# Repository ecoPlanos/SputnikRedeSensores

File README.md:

# SputnikRedeSensores

Open source project of a sensors test suit.

The goal is to develop a system to compare several sensors of each type out of several types.
The sensors will be assembled on a PCB for each type, that will connect to an Arduino Due compatible shield.
A program running on the Arduino, will log sensors data to a SD card and make it accessible through a FTP server.

types of sensors:
Temperature and relative humidity;
Superficial temperature;
Motion detection;
Air quality;
Electrical current;
Water flow;
Proximity;
Distance;
Microwave;
Lumen;
UV.

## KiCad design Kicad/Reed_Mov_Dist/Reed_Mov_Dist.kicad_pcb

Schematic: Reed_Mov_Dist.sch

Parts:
C1: 10uF; CP_Radial_D4.0mm_P2.00mm
C2: 220uF; CP_Radial_D7.5mm_P2.50mm
D1: D; D_T-1_P5.08mm_Horizontal
J1: Barrel_Jack; BARREL_JACK
J2, J3, J4, J13: Conn_01x02; Socket_Strip_Straight_1x02_Pitch2.54mm
J5: LIS3DH_1; Socket_Strip_Straight_1x06_Pitch2.54mm
J6: ITG3200; Socket_Strip_Straight_1x06_Pitch2.54mm
J7: LIS3DH_2; Socket_Strip_Straight_1x06_Pitch2.54mm
J8: TTL_Level_Shifter_1; Socket_Strip_Straight_1x06_Pitch2.54mm
J9: TTL_Level_Shifter_2; Socket_Strip_Straight_1x06_Pitch2.54mm
J10: HC-SRO4; Socket_Strip_Straight_1x04_Pitch2.54mm
J11: URM37; Socket_Strip_Straight_1x09_Pitch2.54mm
J12: LV-MaxSonar-EZ1; Socket_Strip_Straight_1x07_Pitch2.54mm
R1, R2, R3: 1K; R_Axial_DIN0207_L6.3mm_D2.5mm_P7.62mm_Horizontal
U1: LM7805_TO220; TO-220-3_Vertical
U2: XBEE
uP1: ARDUPROMINI-6; ArduProMini-6

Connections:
3V3: J6.1, J7.5, J8.1, J12.6, J13.2, R1.1, R2.1, R3.1, uP1.22
3V3_Xbee: J13.1, U2.1 (VCC)
5V: C1.1, J9.1, J10.1, J11.9, U1.3 (VO), uP1.19
ADC_EZ1: J12.3, uP1.26
ECHO_EZ1: J12.2, uP1.25
ECHO_HC: J8.3, uP1.16
ECHO_HC_HV: J9.3, J10.3
ECHO_URM: J8.5, uP1.18
ECHO_URM_HV: J9.5, J11.6
GND: C1.2, C2.2, J1.2, J1.3, J2.1, J3.1, J4.1, J5.6, J6.2, J7.6, J8.6, J9.6, J10.4, J11.8, J12.7, U1.2 (GND), U2.10 (GND), uP1.10, uP1.20
unnamed: C2.1, D1.1 (K), U1.1 (VI)
unnamed: D1.2 (A), J1.1
Reed_Big_White: J3.2, R2.2, uP1.12
Reed_Red: J2.2, R1.2, uP1.11
Reed_Small_White: J4.2, R3.2, uP1.13
Rx: U2.2 (DOUT), uP1.8
SCL: J6.4, J7.3, uP1.31
SDA: J6.3, J7.4, uP1.32
TRIG_EZ1: J12.4, uP1.29
TRIG_HC: J8.2, uP1.15
TRIG_HC_HV: J9.2, J10.2
TRIG_URM: J8.4, uP1.17
TRIG_URM_HV: J9.4, J11.4
Tx: U2.3 (DIN), uP1.7

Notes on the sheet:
Reed Sensors
Arduino Pro Mini
Distance Sensors
Accelerometers
Power Supply

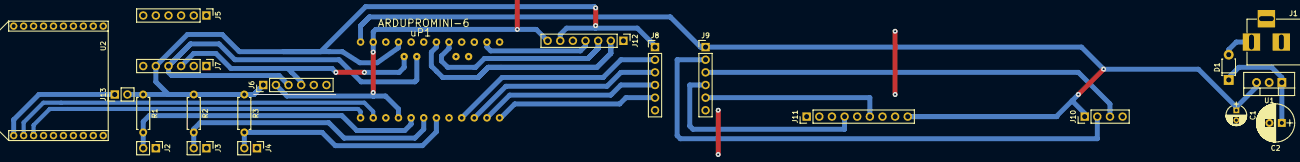
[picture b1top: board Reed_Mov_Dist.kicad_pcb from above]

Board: 2 copper layers, 22 parts (0 on the bottom side), 24 nets.

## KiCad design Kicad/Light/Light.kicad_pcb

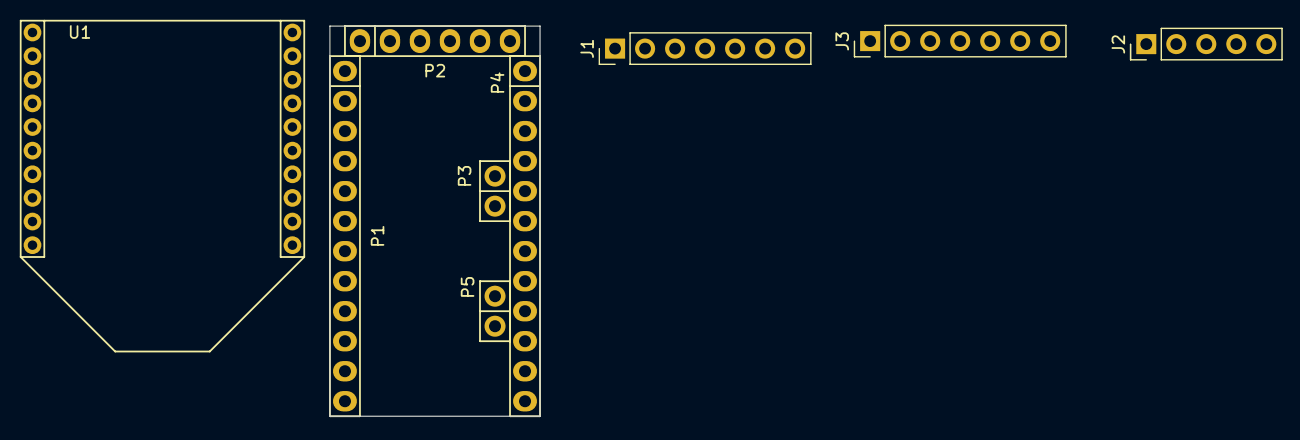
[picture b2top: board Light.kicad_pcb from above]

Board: 2 copper layers, 17.8 x 33.0 mm, 9 parts (0 on the bottom side), 8 nets, no tracks yet.

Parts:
J1: TSL2561; Socket_Strip_Straight_1x07_Pitch2.54mm
J2: ISL29125; Socket_Strip_Straight_1x05_Pitch2.54mm
J3: SI1145; Socket_Strip_Straight_1x07_Pitch2.54mm
P1: Digital; Socket_Strip_Arduino_1x12
P2: COM; Socket_Strip_Arduino_1x06
P3, P5: ADC; Socket_Strip_Arduino_1x02
P4: Analog; Socket_Strip_Arduino_1x12
U1: XBEE

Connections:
3V3: J1.5, J2.4, J3.5, P2.4, P4.4, U1.1
/Reset: P1.3, P4.3
GND: J1.4, J1.6, J2.5, J3.6, P1.4, P2.5, P2.6, P4.2, U1.10
ISL29125_nINT: J2.1, P1.5
RX: P1.2, P2.3, U1.2
SCL: J1.1, J2.2, J3.2, P3.1
SDA: J1.2, J2.3, J3.1, P3.2
TX: P1.1, P2.2, U1.3

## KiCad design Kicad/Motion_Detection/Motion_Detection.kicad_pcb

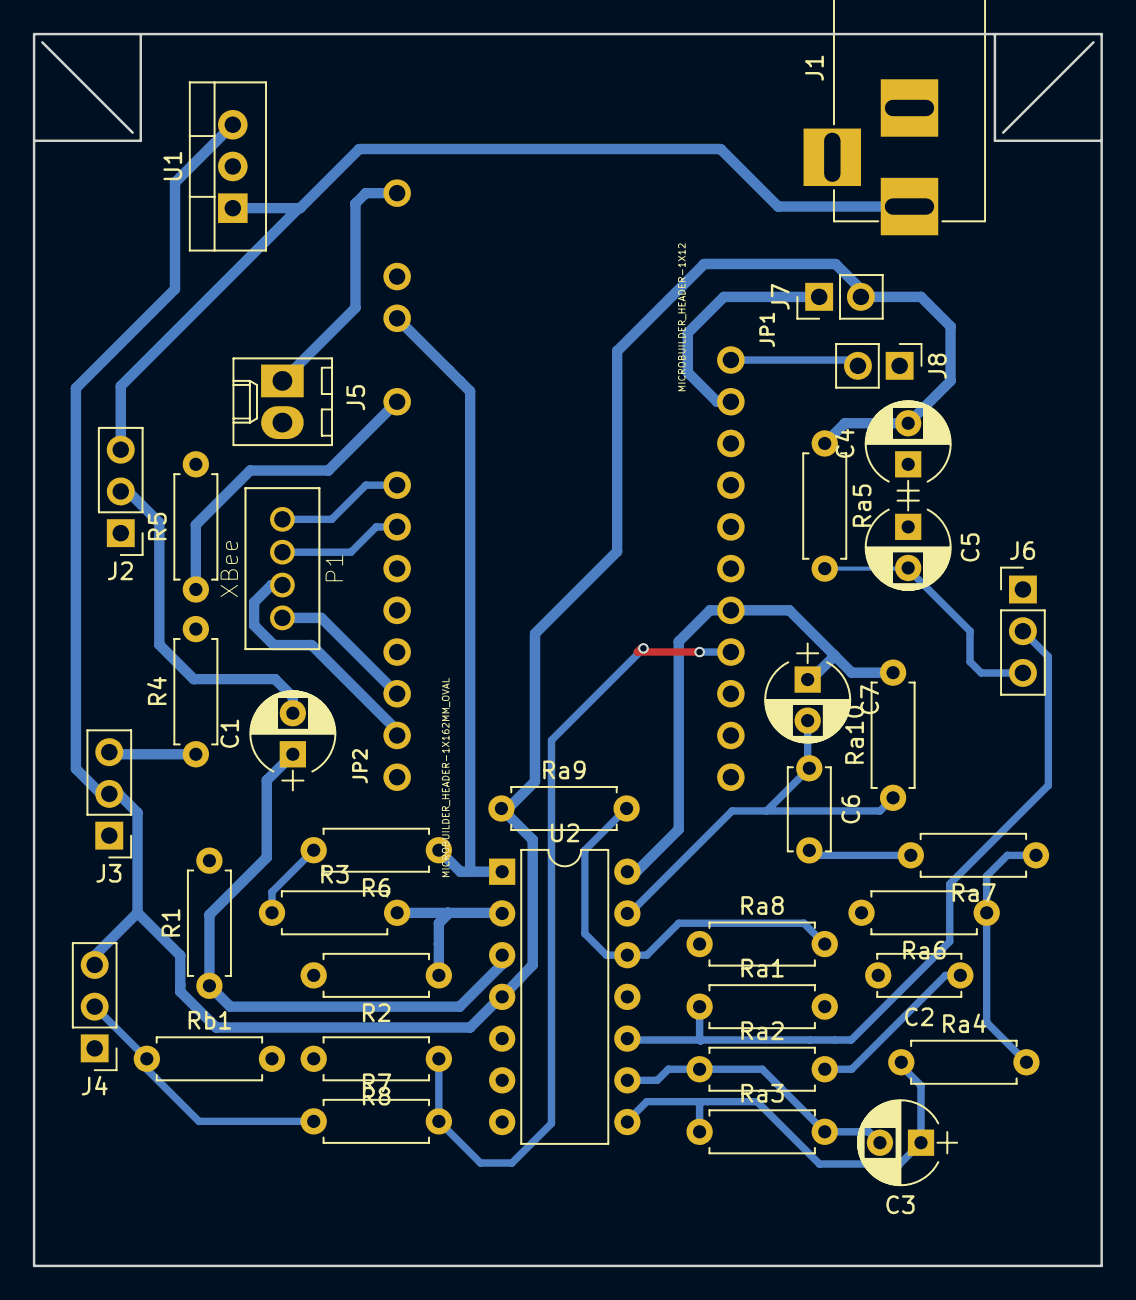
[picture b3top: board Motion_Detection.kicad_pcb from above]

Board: 2 copper layers, 65.0 x 75.0 mm, 39 parts (0 on the bottom side), 29 nets.

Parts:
C1: 22u; CP_Radial_D5.0mm_P2.50mm
C2, C6: 10u; C_Disc_D5.0mm_W2.5mm_P5.00mm
C3, C7: 10n; CP_Radial_D5.0mm_P2.50mm
C4: 100u; CP_Radial_D5.0mm_P2.50mm
C5: 10u; CP_Radial_D5.0mm_P2.50mm
J1: 12V input; BARREL_JACK
J2: SE-10; Pin_Header_Straight_1x03_Pitch2.54mm
J3: SEN0192_MW; Pin_Header_Straight_1x03_Pitch2.54mm
J4: EKMB; Pin_Header_Straight_1x03_Pitch2.54mm
J5: 3V3 Output; Molex_KK-6410-02_02x2.54mm_Straight
J6: ZRE200GE; Pin_Header_Straight_1x03_Pitch2.54mm
J7: 5V Ext; Pin_Header_Straight_1x02_Pitch2.54mm
J8: 3V3 EN; Pin_Header_Straight_1x02_Pitch2.54mm
JP1: MICROBUILDER_HEADER-1X12; MICROBUILDER_1X12_ROUND
JP2: MICROBUILDER_HEADER-1X162MM_OVAL; MICROBUILDER_1X16_ROUND
P1: XBee; JST_PHR-4
R1: 4.62K; R_Axial_DIN0207_L6.3mm_D2.5mm_P7.62mm_Horizontal
R2: 9.85K; R_Axial_DIN0207_L6.3mm_D2.5mm_P7.62mm_Horizontal
R3: 9.87K; R_Axial_DIN0207_L6.3mm_D2.5mm_P7.62mm_Horizontal
R4, R7: 1.491K; R_Axial_DIN0207_L6.3mm_D2.5mm_P7.62mm_Horizontal
R5, R8: 2.18K; R_Axial_DIN0207_L6.3mm_D2.5mm_P7.62mm_Horizontal
R6: 14.82K; R_Axial_DIN0207_L6.3mm_D2.5mm_P7.62mm_Horizontal
Ra1: 47K; R_Axial_DIN0207_L6.3mm_D2.5mm_P7.62mm_Horizontal
Ra2, Ra7: 10K; R_Axial_DIN0207_L6.3mm_D2.5mm_P7.62mm_Horizontal
Ra3, Ra6: 1M; R_Axial_DIN0207_L6.3mm_D2.5mm_P7.62mm_Horizontal
Ra4: 100K; R_Axial_DIN0207_L6.3mm_D2.5mm_P7.62mm_Horizontal
Ra5: 1K; R_Axial_DIN0207_L6.3mm_D2.5mm_P7.62mm_Horizontal
Ra8: 470K; R_Axial_DIN0207_L6.3mm_D2.5mm_P7.62mm_Horizontal
Ra9: 810K; R_Axial_DIN0207_L6.3mm_D2.5mm_P7.62mm_Horizontal
Ra10: 1M2; R_Axial_DIN0207_L6.3mm_D2.5mm_P7.62mm_Horizontal
Rb1: 10K; R_Axial_DIN0207_L6.3mm_D2.5mm_P7.62mm_Horizontal
U1: LM7805_TO220; TO-220-3_Vertical
U2: LM324; DIP-14_W7.62mm

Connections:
3V3: J5.1, JP2.15
5V: C4.2, J3.2, J4.3, J7.2, Ra5.1, Ra9.1, U1.3, U2.4
12V: J1.1, J2.3, U1.1
EKMB_OUT: J4.2, R7.1, Rb1.1
EKMB_OUT_: JP1.9, R7.2, R8.1
EN: J8.2, JP1.2
GND: C2.2, C4.1, C5.1, J1.2, J1.3, J2.1, J3.1, J4.1, J5.2, J6.1, J8.1, JP2.1, JP2.13, R1.2, R2.2, R5.2, R8.2, Ra1.2, Ra6.2, Ra8.1, Rb1.2, U1.2, U2.11
unnamed: C1.1, R1.1, U2.3
unnamed: C2.1, Ra2.2
unnamed: C3.1, Ra3.1, Ra4.1, U2.8
unnamed: C3.2, Ra2.1, Ra3.2, U2.9
unnamed: C5.2, J6.3, Ra5.2
unnamed: C6.1, C7.2, Ra10.1, U2.13
unnamed: C6.2, Ra7.2
unnamed: R2.1, R3.2, U2.2
unnamed: R3.1, R6.2
unnamed: Ra4.2, Ra6.1, Ra7.1
unnamed: Ra8.2, Ra9.2, U2.12
RX: JP2.3, P1.4
SE-10_OUT: C1.2, J2.2
SE-10_OUT_: JP2.12, R6.1, U2.1
SEN0192_OUT: J3.3, R4.1
SEN0192_OUT_: JP2.10, R4.2, R5.1
TX: JP2.2, P1.3
VBUS: J7.1, JP1.3
XBee_ON: JP2.8, P1.1
XBee_nRESET: JP2.7, P1.2
ZRE200_OUT: J6.2, Ra1.1, U2.10
ZRE200_OUT_: C7.1, JP1.8, Ra10.2, U2.14

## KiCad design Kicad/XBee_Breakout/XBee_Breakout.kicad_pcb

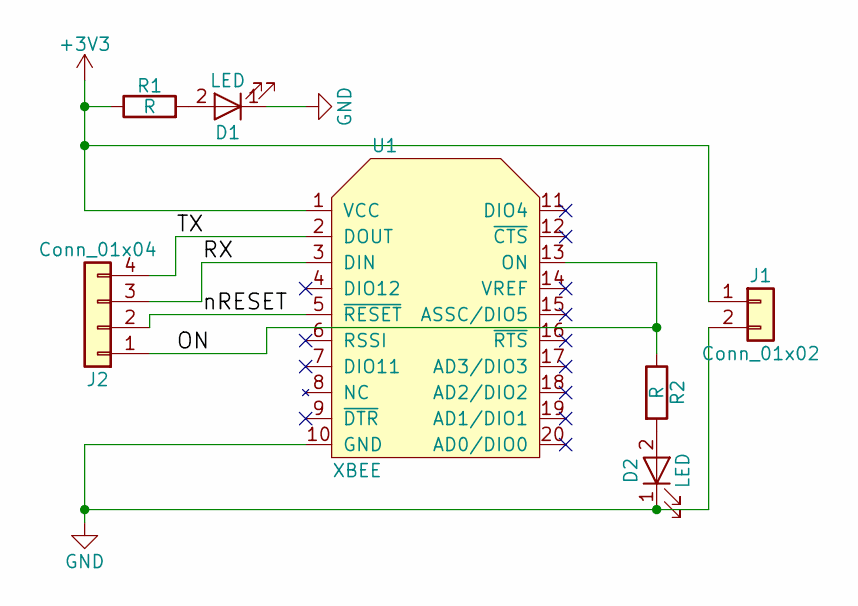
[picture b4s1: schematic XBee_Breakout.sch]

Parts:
D1, D2: LED; LED_D4.0mm
J1: Conn_01x02; Molex_KK-6410-02_02x2.54mm_Straight
J2: Conn_01x04; JST_PHR-4
R1, R2: R; R_Axial_DIN0207_L6.3mm_D2.5mm_P7.62mm_Horizontal
U1: XBEE

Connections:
+3V3: J1.1, R1.1, U1.1 (VCC)
/ON: J2.1, R2.1, U1.13 (ON)
/RX: J2.3, U1.3 (DIN)
/TX: J2.4, U1.2 (DOUT)
/nRESET: J2.2, U1.5 (~RESET)
GND: D1.1 (K), D2.1 (K), J1.2, U1.10 (GND)
unnamed: D1.2 (A), R1.2
unnamed: D2.2 (A), R2.2

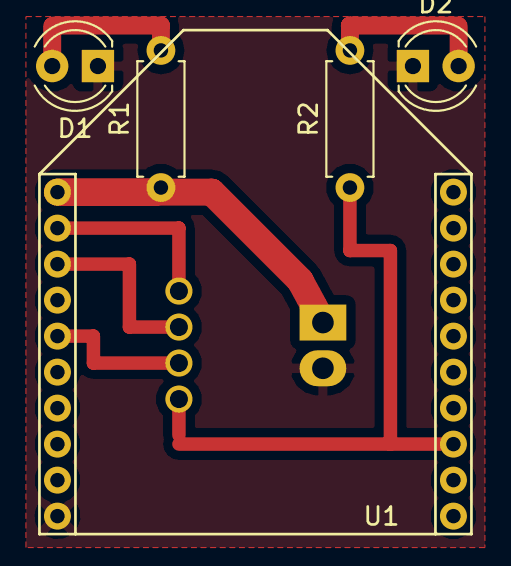
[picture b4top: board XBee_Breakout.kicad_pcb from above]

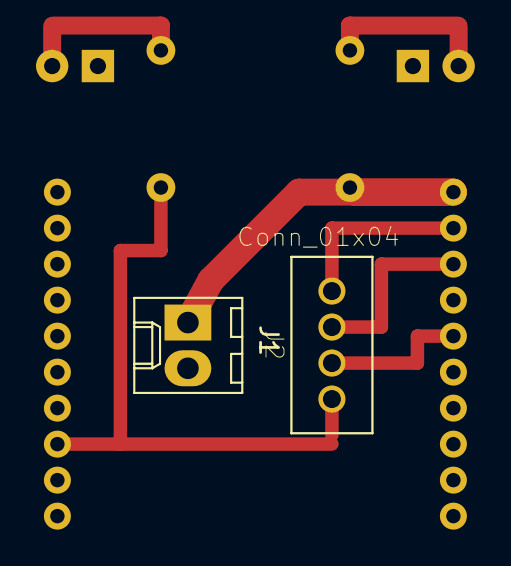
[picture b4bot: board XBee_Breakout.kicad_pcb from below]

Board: 2 copper layers, 7 parts (2 on the bottom side), 8 nets.

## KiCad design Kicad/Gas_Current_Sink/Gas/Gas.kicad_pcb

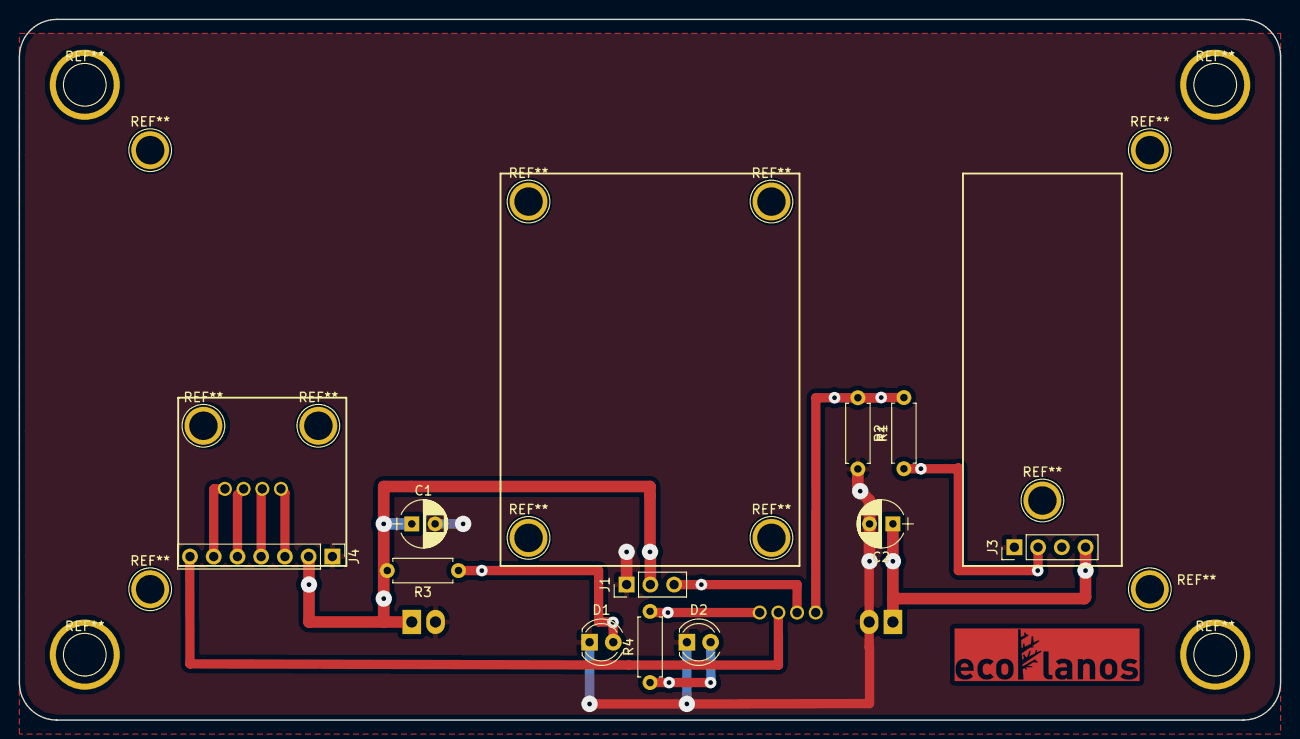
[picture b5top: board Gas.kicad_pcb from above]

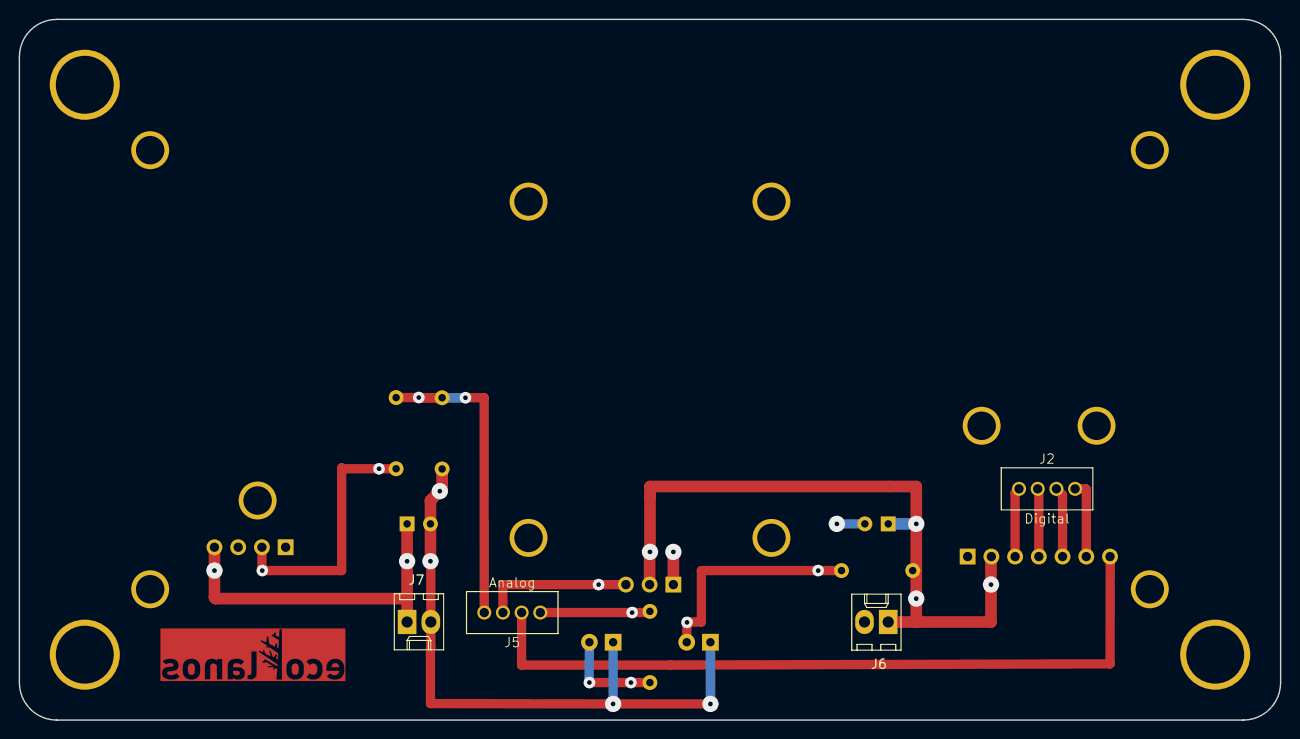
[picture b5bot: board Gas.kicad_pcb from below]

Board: 2 copper layers, 135.0 x 75.0 mm, 15 parts (4 on the bottom side), 14 nets.

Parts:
C1, C2: CP; CP_Radial_D5.0mm_P2.50mm
D1, D2: LED; LED_D4.0mm
J1: MG811; Pin_Header_Straight_1x03_Pitch2.54mm
J2: Digital; JST_PHR-4
J3: MQ135; Pin_Header_Straight_1x04_Pitch2.54mm
J4: CCS811; Pin_Header_Straight_1x07_Pitch2.54mm
J5: Analog; JST_PHR-4
J6, J7: CONN_01X02; Molex_KK-6410-02_02x2.54mm_Straight
R1: 6K8; R_Axial_DIN0207_L6.3mm_D2.5mm_P7.62mm_Horizontal
R2: 13K2; R_Axial_DIN0207_L6.3mm_D2.5mm_P7.62mm_Horizontal
R3, R4: R; R_Axial_DIN0207_L6.3mm_D2.5mm_P7.62mm_Horizontal

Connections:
+3V3: C1.1, J1.2, J4.2, J6.1, R3.2
+5V: C2.1, J3.4, J7.1
/MG811_out: J1.3, J5.3
/MQ135_out_5v: J3.2, R1.1
/SCL: J2.2, J4.4
/SDA: J2.1, J4.3
/nINT: J2.4, J4.6
/nRST: J4.7, J5.2
/nWAKE: J2.3, J4.5
GND: C1.2, C2.2, D1.1, D2.1, J1.1, J3.1, J4.1, J6.2, J7.2, R2.2
MQ135_out_3V3: J5.4, R1.2, R2.1
unnamed: D1.2, R3.1
unnamed: D2.2, R4.1
unnamed: J5.1, R4.2

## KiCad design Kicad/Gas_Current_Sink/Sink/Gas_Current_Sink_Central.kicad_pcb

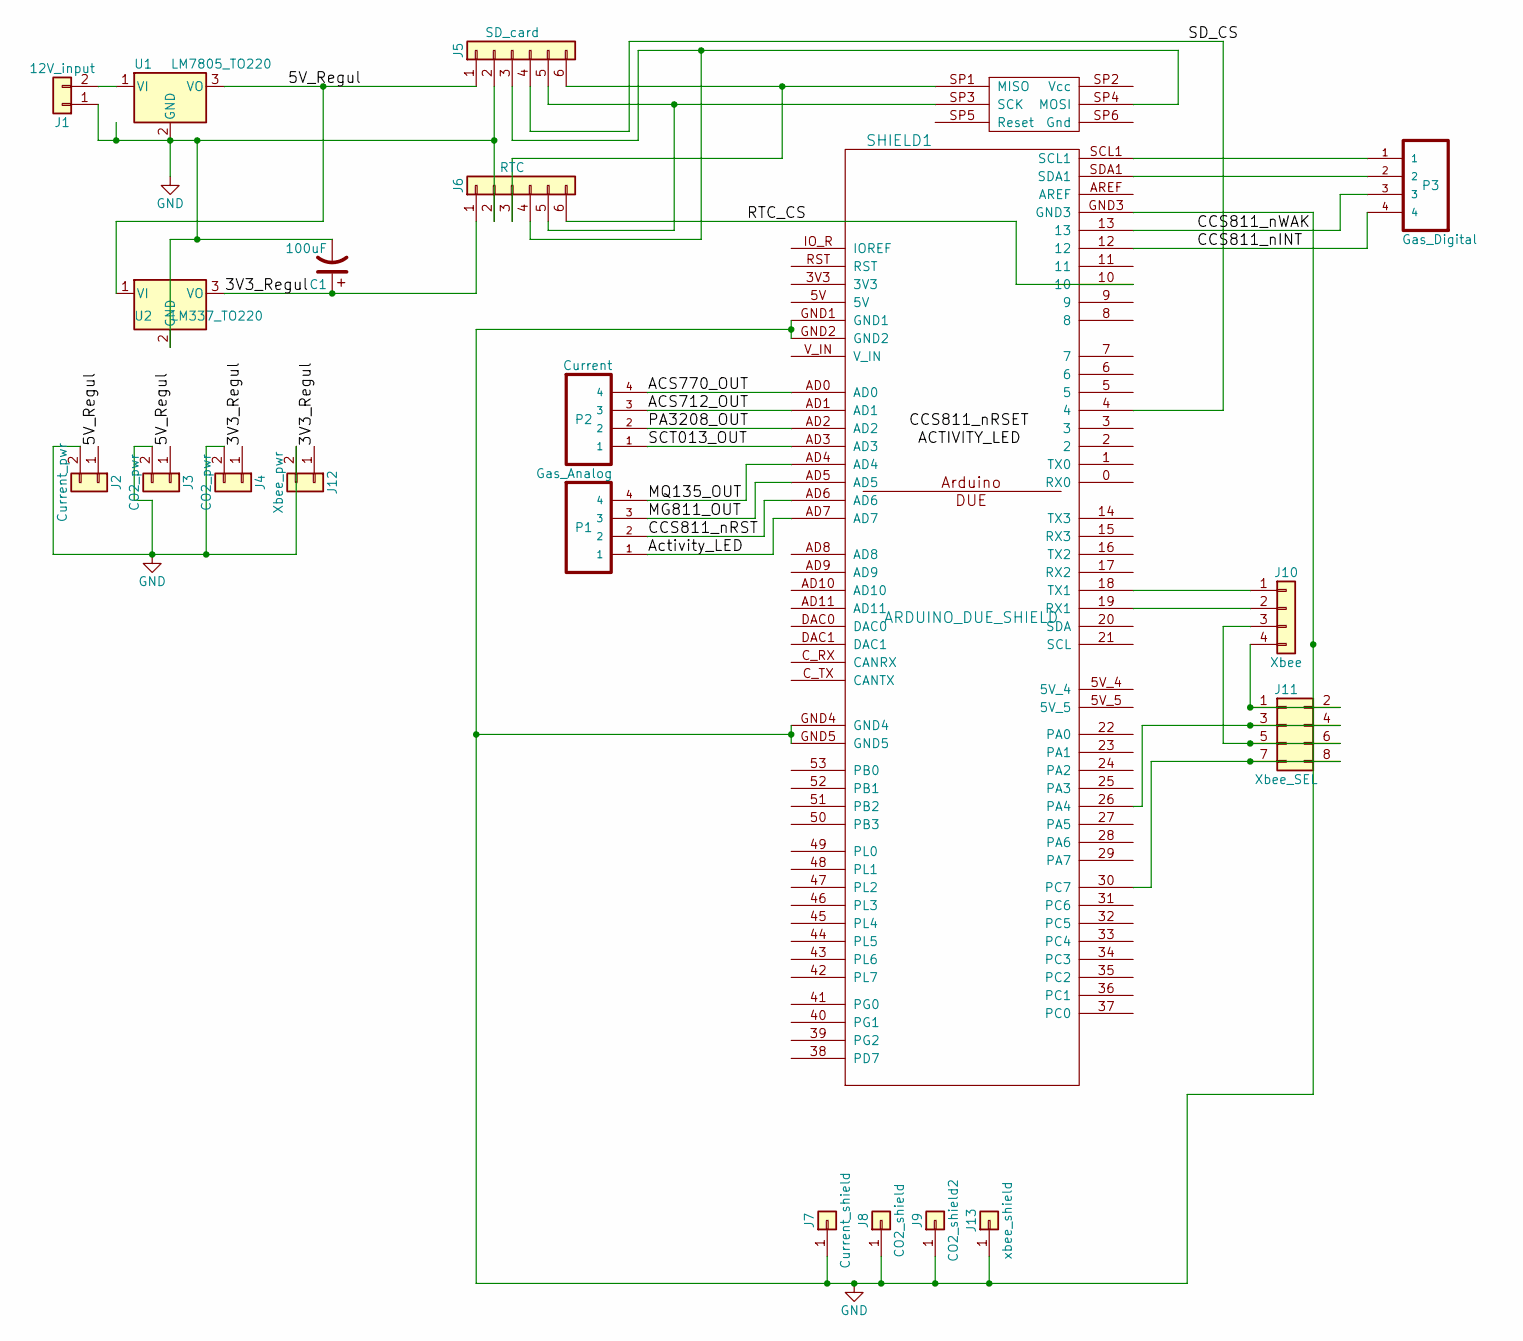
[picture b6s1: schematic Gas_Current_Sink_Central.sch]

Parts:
C1: 100uF; CP_Radial_Tantal_D10.5mm_P5.00mm
J1: 12V_input; Molex_KK-6410-02_02x2.54mm_Straight
J2: Current_pwr; Molex_KK-6410-02_02x2.54mm_Straight
J3, J4: CO2_pwr; Molex_KK-6410-02_02x2.54mm_Straight
J5: SD_card; Pin_Header_Straight_1x06_Pitch2.54mm
J6: RTC; Socket_Strip_Angled_1x06_Pitch2.54mm
J7: Current_shield; Socket_Strip_Angled_1x01_Pitch2.54mm
J8: CO2_shield; Socket_Strip_Straight_1x01_Pitch2.54mm
J9: CO2_shield2; Socket_Strip_Straight_1x01_Pitch2.54mm
J10: Xbee; JST_PHR-4
J11: Xbee_SEL; Pin_Header_Straight_2x04_Pitch2.54mm
J12: Xbee_pwr; Molex_KK-6410-02_02x2.54mm_Straight
J13: xbee_shield; Socket_Strip_Straight_1x01_Pitch2.54mm
P1: Gas_Analog; JST_PHR-4
P2: Current; JST_PHR-4
P3: Gas_Digital; JST_PHR-4
SHIELD1: ARDUINO_DUE_SHIELD
U1: LM7805_TO220; TO-220-3_Vertical
U2: LM337_TO220; TO-220-3_Vertical

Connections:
/3V3_Regul: C1.1, J4.1, J6.1, J12.1, U2.3 (VO)
/5V_Regul: J2.1, J3.1, J5.1, U1.3 (VO), U2.1 (VI)
/ACS712_OUT: P2.3, SHIELD1.AD1
/ACS770_OUT: P2.4, SHIELD1.AD0
/CCS811_nINT: P3.4, SHIELD1.12
/CCS811_nWAK: P3.3, SHIELD1.13
/MG811_OUT: P1.3, SHIELD1.AD5
/MQ135_OUT: P1.4, SHIELD1.AD4
/PA3208_OUT: P2.2, SHIELD1.AD2
/RTC_CS: J6.6, SHIELD1.10
/SCT013_OUT: P2.1, SHIELD1.AD3
/SD_CS: J5.4, SHIELD1.4
GND: C1.2, J1.1, J2.2, J3.2, J4.2, J5.2, J6.2, J7.1, J8.1, J9.1, J12.2, J13.1, SHIELD1.GND1, SHIELD1.GND2, SHIELD1.GND3, SHIELD1.GND4, SHIELD1.GND5, U1.2 (GND), U2.2 (GND)
unnamed: J1.2, U1.1 (VI)
unnamed: J5.3, J6.4, SHIELD1.SP4 (MOSI)
unnamed: J5.5, J6.5, SHIELD1.SP3 (SCK)
unnamed: J5.6, J6.3, SHIELD1.SP1 (MISO)
unnamed: J10.1, SHIELD1.18 (TX1)
unnamed: J10.2, SHIELD1.19 (RX1)
unnamed: J10.3, J11.5, J11.6
unnamed: J10.4, J11.1, J11.2
unnamed: J11.3, J11.4, SHIELD1.26 (PA4)
unnamed: J11.7, J11.8, SHIELD1.30 (PC7)
unnamed: P1.1, SHIELD1.AD7
unnamed: P1.2, SHIELD1.AD6
unnamed: P3.1, SHIELD1.SCL1
unnamed: P3.2, SHIELD1.SDA1

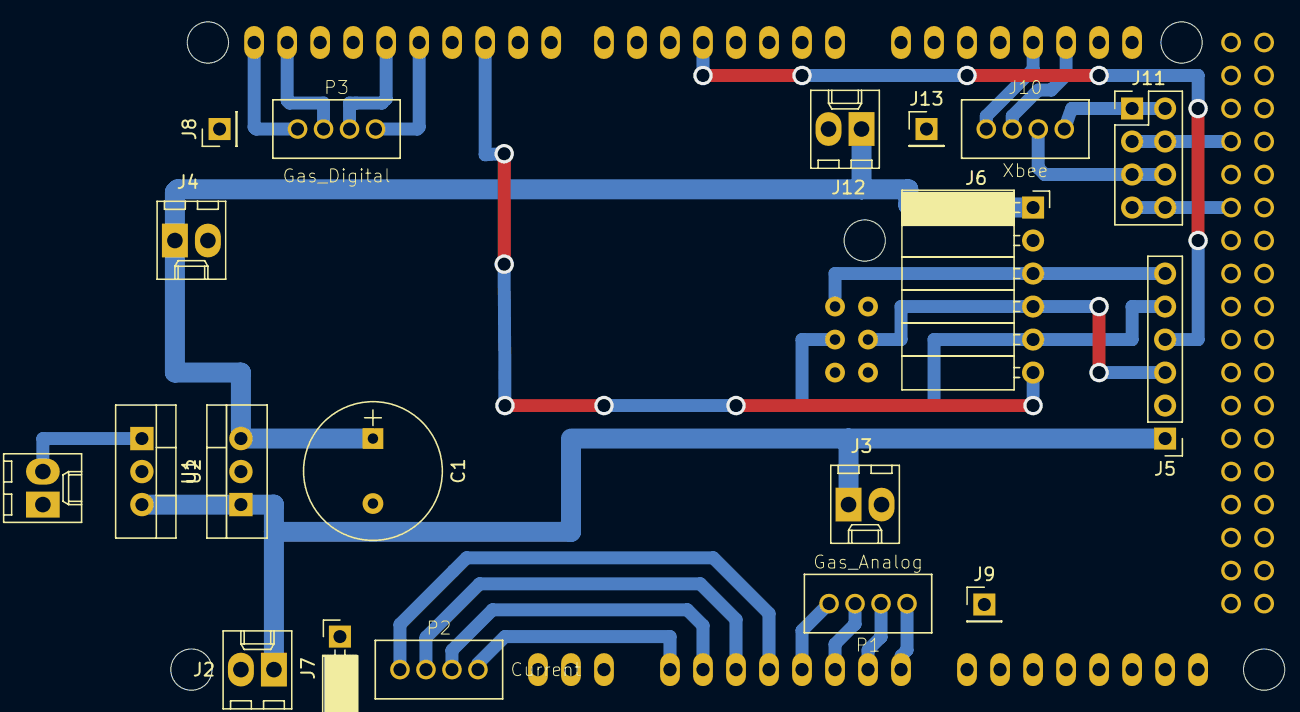
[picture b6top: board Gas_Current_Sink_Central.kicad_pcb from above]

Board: 2 copper layers, 20 parts (0 on the bottom side), 27 nets.

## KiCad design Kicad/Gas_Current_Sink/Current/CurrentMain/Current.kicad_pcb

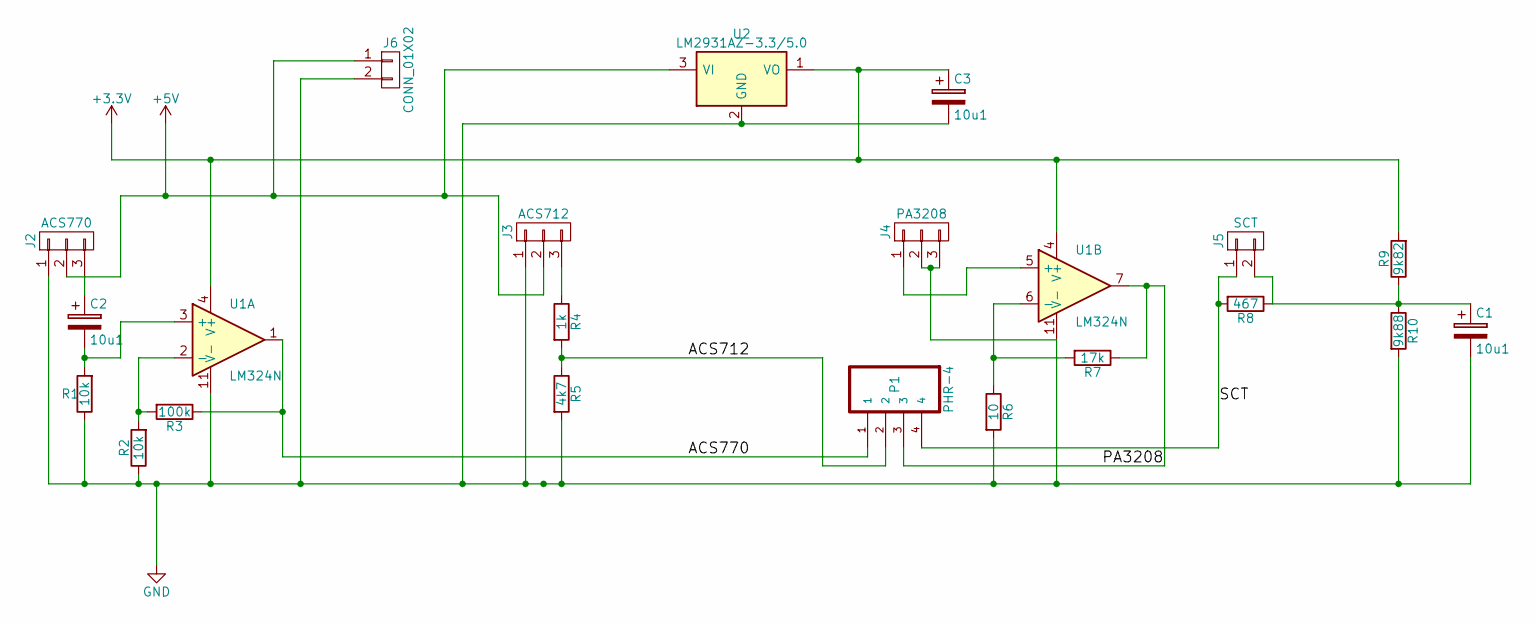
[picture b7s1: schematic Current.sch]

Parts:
C1, C2: 10u1; CP_Radial_D5.0mm_P2.50mm
C3: 10u1; CP_Radial_Tantal_D9.0mm_P5.00mm
J2: ACS770; Pin_Header_Straight_1x03_Pitch2.54mm
J3: ACS712; Pin_Header_Straight_1x03_Pitch2.54mm
J4: PA3208; Pin_Header_Straight_1x03_Pitch2.54mm
J5: SCT; Pin_Header_Straight_1x02_Pitch2.54mm
J6: CONN_01X02; Molex_KK-6410-02_02x2.54mm_Straight
P1: PHR-4; JST_PHR-4
R1, R2: 10k; R_Axial_DIN0207_L6.3mm_D2.5mm_P7.62mm_Horizontal
R3: 100k; R_Axial_DIN0207_L6.3mm_D2.5mm_P7.62mm_Horizontal
R4: 1k; R_Axial_DIN0207_L6.3mm_D2.5mm_P7.62mm_Horizontal
R5: 4k7; R_Axial_DIN0207_L6.3mm_D2.5mm_P7.62mm_Horizontal
R6: 10; R_Axial_DIN0207_L6.3mm_D2.5mm_P7.62mm_Horizontal
R7: 17k; R_Axial_DIN0207_L6.3mm_D2.5mm_P7.62mm_Horizontal
R8: 467; R_Axial_DIN0207_L6.3mm_D2.5mm_P7.62mm_Horizontal
R9: 9k82; R_Axial_DIN0207_L6.3mm_D2.5mm_P7.62mm_Horizontal
R10: 9k88; R_Axial_DIN0207_L6.3mm_D2.5mm_P7.62mm_Horizontal
U1: LM324N; DIP-14_W7.62mm
U2: LM2931AZ-3.3/5.0; TO-220_Vertical

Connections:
+3V3: C3.1, R9.2, U1.4 (V+), U2.1 (VO)
+5V: J2.2, J3.2, J6.1, U2.3 (VI)
/ACS712: P1.2, R4.2, R5.1
/ACS770: P1.1, R3.1, U1.1
/PA3208: P1.3, R7.1, U1.7
/SCT: J5.1, P1.4, R8.2
GND: C1.2, C3.2, J2.1, J3.1, J4.2, J4.3, J6.2, R1.1, R2.1, R5.2, R6.2, R10.2, U1.11 (V-), U2.2 (GND)
unnamed: C1.1, J5.2, R8.1, R9.1, R10.1
unnamed: C2.1, J2.3
unnamed: C2.2, R1.2, U1.3 (+)
unnamed: J3.3, R4.1
unnamed: J4.1, U1.5 (+)
unnamed: R2.2, R3.2, U1.2 (-)
unnamed: R6.1, R7.2, U1.6 (-)

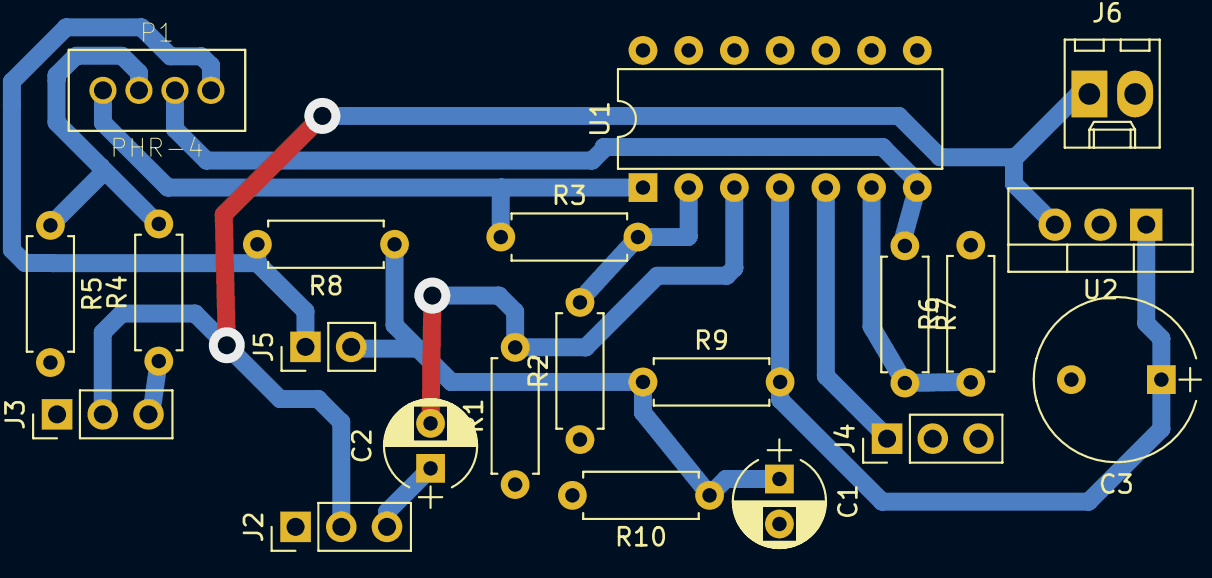
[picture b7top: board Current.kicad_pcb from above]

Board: 2 copper layers, 21 parts (0 on the bottom side), 14 nets.

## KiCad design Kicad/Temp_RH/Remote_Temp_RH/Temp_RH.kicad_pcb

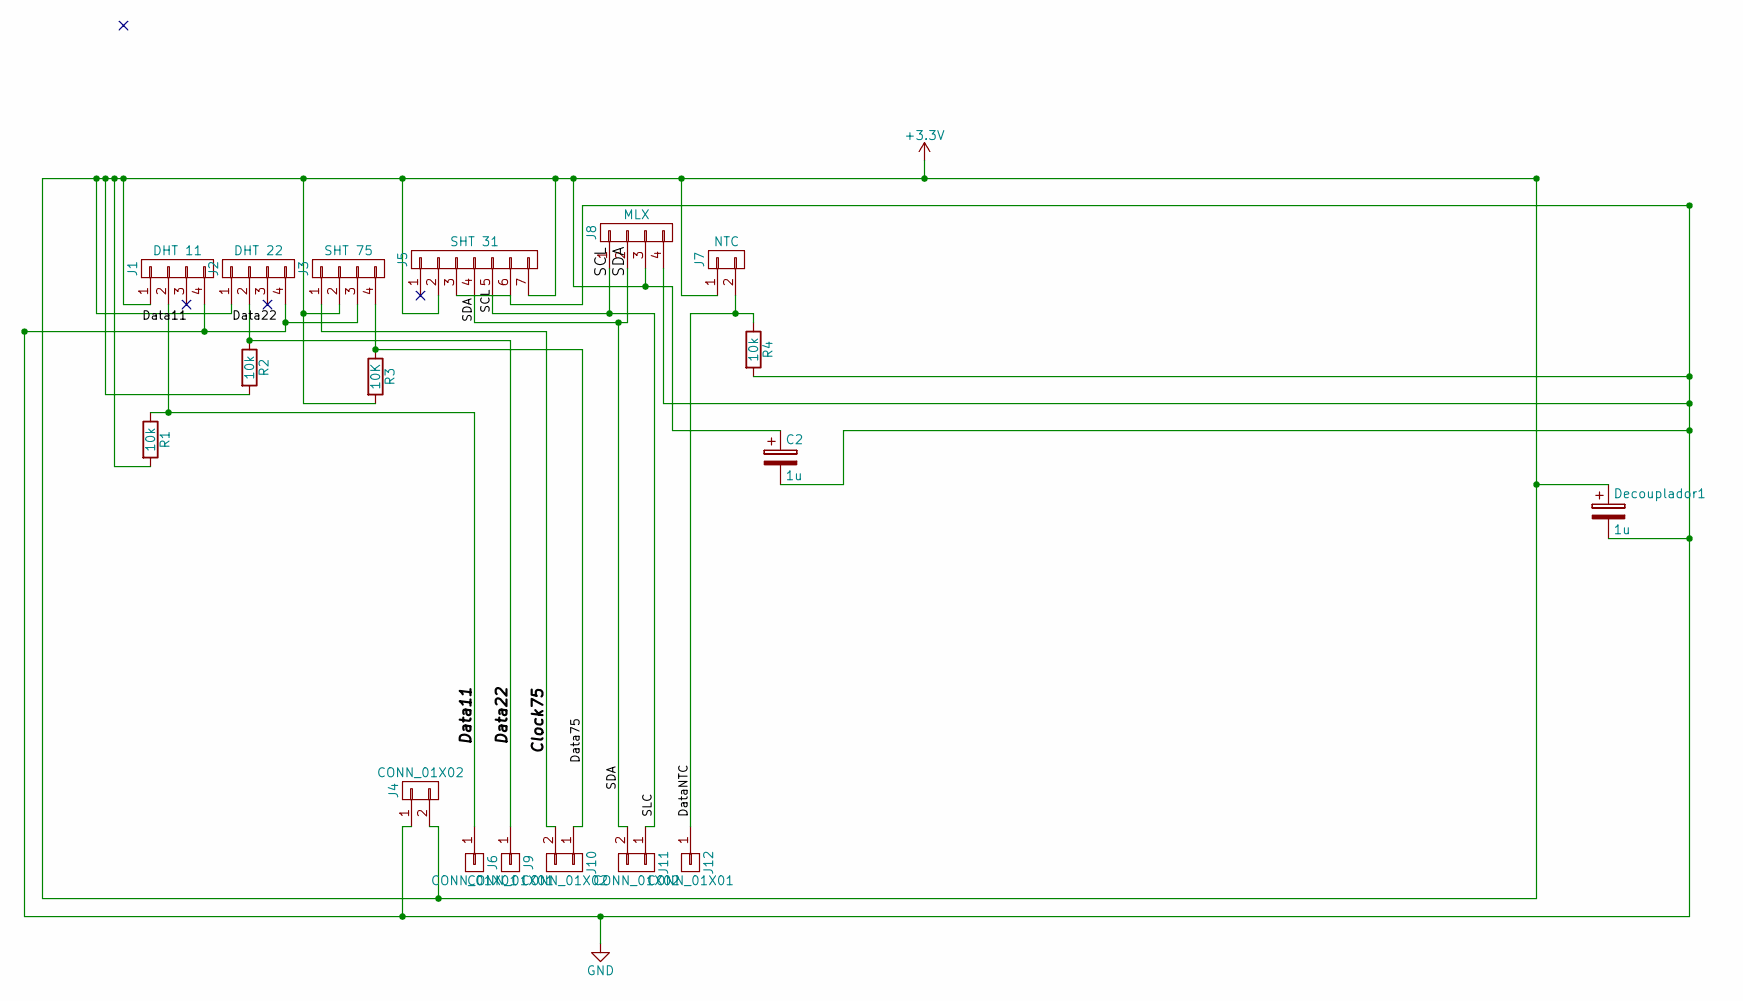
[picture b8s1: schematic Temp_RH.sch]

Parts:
C2: 1u; CP_Radial_D5.0mm_P2.50mm
Decouplador1: 1u; CP_Radial_D5.0mm_P2.50mm
J1: DHT 11; Pin_Header_Straight_1x04_Pitch2.54mm
J2: DHT 22; Pin_Header_Straight_1x04_Pitch2.54mm
J3: SHT 75; Pin_Header_Straight_1x04_Pitch2.54mm
J4, J10, J11: CONN_01X02; Pin_Header_Straight_1x02_Pitch2.54mm
J5: SHT 31; Pin_Header_Straight_1x07_Pitch2.54mm
J6, J9, J12: CONN_01X01; Pin_Header_Straight_1x01_Pitch2.54mm
J7: NTC; Pin_Header_Straight_1x02_Pitch2.54mm
J8: MLX; Pin_Header_Straight_1x04_Pitch2.54mm
R1, R2, R4: 10k; R_Axial_DIN0204_L3.6mm_D1.6mm_P5.08mm_Horizontal
R3: 10K; R_Axial_DIN0204_L3.6mm_D1.6mm_P5.08mm_Horizontal

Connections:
+3V3: C2.1, Decouplador1.1, J1.1, J2.1, J3.2, J4.2, J5.2, J5.7, J7.1, J8.3, R1.2, R2.2, R3.2
/Clock75: J3.1, J10.2
/Data11: J1.2, J6.1, R1.1
/Data22: J2.2, J9.1, R2.1
/Data75: J3.4, J10.1, R3.1
/DataNTC: J7.2, J12.1, R4.1
/SCL: J5.5, J8.1, J11.1
/SDA: J5.4, J8.2, J11.2
GND: C2.2, Decouplador1.2, J1.4, J2.4, J3.3, J4.1, J5.3, J5.6, J8.4, R4.2

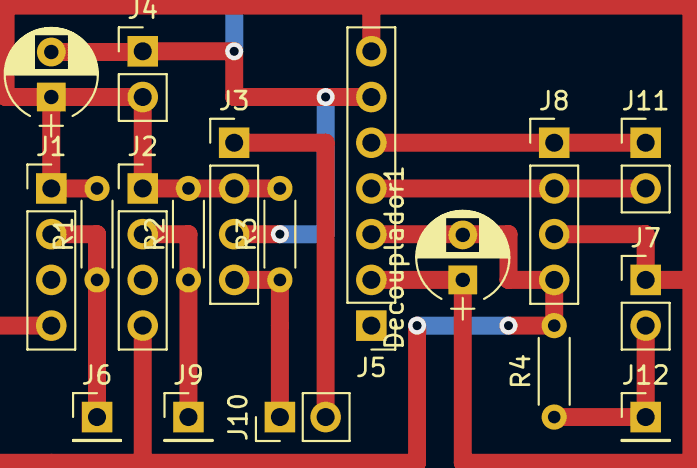
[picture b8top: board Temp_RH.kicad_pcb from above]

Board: 2 copper layers, 18 parts (0 on the bottom side), 9 nets.

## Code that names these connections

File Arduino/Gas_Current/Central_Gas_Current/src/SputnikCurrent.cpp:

#include "SputnikCurrent.h"

analog_sensor acs770, acs712, pa3208, sct013;
float_t acs770_current_rms, acs712_current_rms, pa3208_current_rms, sct013_current_rms;

void sputnikCurrentInit(void)
{
  acs770 = analog_sensor(ACS770_PIN);
  acs712 = analog_sensor(ACS712_PIN);
  pa3208 = analog_sensor(PA3208_PIN);
  sct013 = analog_sensor(SCT013_PIN);
  pinMode(ACS770_PIN,INPUT);
  pinMode(ACS712_PIN,INPUT);
  pinMode(PA3208_PIN,INPUT);
  pinMode(SCT013_PIN,INPUT);
}

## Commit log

2017-06-10 Hello world dos commit o comuna não sabe fazer pipocas
2017-06-10 adicao readme
2017-06-10 teste
2017-06-10 removido teste
2017-06-10 Removido teste do Rui
2017-06-10 Ao copiar o link do git, selecionar ssh
2017-06-10 Adicionados ficheiros de projeto do Platformio, com os arduinos que vão ser utilizados.
2017-06-10 Adicionadas bibliotecas para alguns dos senssores a utilizar. Adicionados ficheiros do projeto em PlatformIO ide.
2017-06-26 Atualizado main.cpp para implementar web server para log de dados. Adicionado comando de compilação do PlatformIO para arduino due
2017-06-28 Adicionadas algumas bibliotecas de sensores. @ST_HW_HC_SR04: Adicionadas funções para calculo de distância.
2017-06-30 Desenvolvido serial logger para sensores DHT11,DHT22 e SHT31.
2017-07-05 Added libs for MLX90614 and SHT75. Configured sht75 and MLX90614.
2017-07-05 Added data logging to SD card. Stable version (HR)!!!
2017-07-10 Added header to main.cpp Added libs for RTC and Wifi.
2017-07-11 Added Kicad project for temperature and relative humidity sensors test board.
2017-07-12 Finished Temperature and RH sensors! MLX temperature sensor is working. Made changes on libraries. Code refactoring.
2017-07-12 Finished Gas sensors implementation and testing. Designed PCB for Gas sensors.
2017-07-14 Added PCB project for T&RH sensors by AndreBotCardoso. Moved Gas sensor's PCB projec directory. Added Main_board PCB project.
2017-07-14 Edited README.md.
2017-07-16 Added air quality sensor to Kicad Gas schematic. Added code for CCS811. Note: arduino program is temporarily not compiling.
2017-07-16 Gas sensor CCS188 was missing and is now programed.
2017-07-17 Added RTC. RTC integration with SD file paths and log files. Added time tag to data log.
2017-07-25 Temperature and Temperature+RH (TTRH) sensors are all implemented. All sensors were tested, except Thermopar temperature sensor. Added TTRH shield schematic and layout (missing SDA1 and SCL1 for SHT7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
2017-07-25 Changes made on the file structure (not yet finished). Added Arduino project for Gas, Current, Motion, Reed and Distance sensors (GCMRD). Modifyed Temp_HR shield to add the MLX sensor.
2017-07-25 Added PT100 conditioning circuit to Tem_HR shield. Ready for testing!
2017-08-08 Revision v1.0! @Arduino/Temp_HR: - Added implentation of thermopar sensor - Added sensors error check routines and recovery Finished file structure changes.Revision v1.0! @Arduino/Temp_HR: - Added im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
2017-08-08 Added Arduino and Kicad projects for Arduino Pro Mini 328. SHT31 is working on the Pro Mini.
2017-08-16 Arduino Pro mini implementation is finished! Arduino Due is only missing a conversion of the input characters from remote station to the CSV format adopted for storage.
2017-08-19 Arduino Release 2.00! Finished implementation of final setup with arduino due and pro mini.
2017-08-21 Resolved ntc bug; Added resistance calculation for NTC; Fixed config file; Added readme.txt auto-write to SD card.
2017-08-22 correcção de caminho no projecto kicad do Gas
2017-08-23 Corrected kicad paths for gas sensors module
2017-08-23 Corrected kicad libraries. Added ecoPlanos libs.
2017-08-23 Added PH4 connectors libs; Finshed CO2 sensors schematic circuit.
2017-08-23 Changed organization of kicad current and gas projects.
2017-08-23 Created Kicad project for the Sink Module
2017-08-23 @Kicad/Gas_Current_Sink/Gas: Finished PCB edge cutting and sensors placement project.
2017-08-24 ecoPlanos 20mm width logo added
2017-08-24 Gas sensors PCB V1.00a
2017-10-03 Store file header on log files; Reset Arduino @ midnight to avoid large data files; Changed loged timestamp to date/time.
2017-10-03 Updated readme file; Fixed loop delay bug.
2017-10-10 dimensionamento cs
2017-10-11 Kicad Current project update Kicad TH project update
2017-10-14 Revision V2.0! New version of remote aquisition system for Temperature and humidity.
2017-10-18 Update to schematic and pcb almost complete (drill holes missing)
2017-10-19 @Gas_Current module - added kicad project for arduino due.
2017-10-19 Minor changes on pcb routing.
2017-10-29 Changed Gas Current kicad directory structure.
2017-10-29 Added some lables to schematic.
2017-11-10 small changes on tem&rh arduino code.
2017-11-10 Current and CO2 Arduino and Kicad Release 1.00! Added Arduino code for CO2 and Current sensor module. Updated Kicad projects for Arduino Due shield and top of the box CO2 PCB.
2017-11-10 Small kicad update.
2017-11-10 Added Kicad projects for XBee module. Added Arduino project for feather M0 board used in the Light and Motion sensor modules.
2017-11-13 CO2 & Current Arduino final release with necessary calibrations. Minor file structure changes.
2017-11-13 Updated gitignore to exclude backup files
2017-11-16 Added XBee breakout board; Added Kicad project for motion sensors; Added script to convert eagle files to kicad; Added feather M0 library converted from eagle to Kicad. Deleted obsolete files.
2017-11-16 Corrected 3V3 bug!
2017-11-17 Updated Kicad Motion detection circuit and board. Updated Feather code to comunicate using XBee.
2017-11-17 Added missing libraries.
2017-11-18 Two new signal conditioning stages were added and the final pcb layout completed.
2017-11-18 @ Motion detection Arduino project - Release 1.00 @ Gas Current Arduino project - added Serial interface to get data from XBee connected Motion sensors.
2017-11-19 Status led pin added to schematic and PCB.
2017-11-20 Added Arduino project for Light sensors module. Changed Gas Current Arduino project to comunicate with the other modules.
2017-11-20 Added light sensors Kicad shield project
2017-11-21 @Arduino/Light .Corrected delay_ms initialization .Added compatibility with feather and arduino pro mini.
2017-11-24 @Arduino - minor bug corrections.
2017-11-29 Schematic and PCB of Reed, Movment and Distance sensors module
2017-11-30 Corrected distance sensors bug. Added jumper to enable or disable Xbee, to access arduino pro mini serial port.
2017-11-30 Corrected SDA and SCL switched bug.
2017-12-04 Added arduino project for distance, accelerometer, gyroscope and reed sensors to monitor windows and blinds motion.
2017-12-05 Changed Gas/Current Arduino project to log different sensor data to different files.
2017-12-05 Gas_Current Arduino bugs correction.
2017-12-06 @Arduino Gas_Current, implemented configuration for multiple sensor modules sampling frequency
2017-12-06 @Arduino Gas_Current project: final bug corrections.
